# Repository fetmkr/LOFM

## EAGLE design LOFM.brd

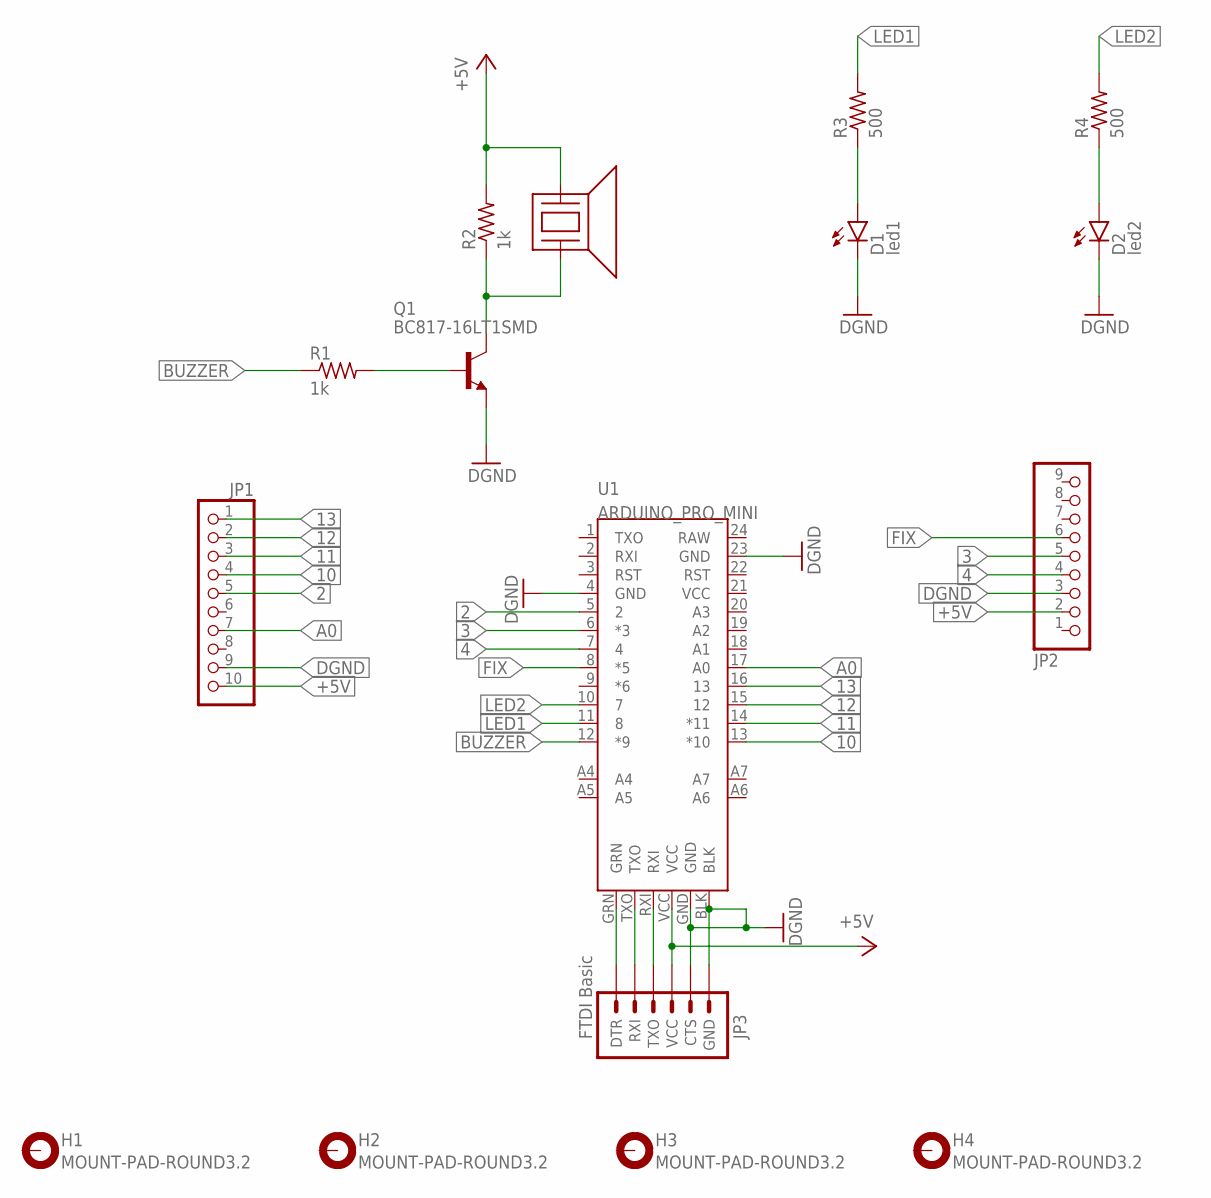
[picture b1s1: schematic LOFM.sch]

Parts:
D1: led1; LED3MM
D2: led2; LED3MM
H1, H2, H3, H4: MOUNT-PAD-ROUND3.2; 3,2-PAD
JP1: HEADER-1X1070MIL; 1X10_ROUND70
JP2: HEADER-1X970MIL; 1X09_ROUND_70
JP3: FTDI Basic; 1X06
Q1: BC817-16LT1SMD; SOT23-BEC
R1, R2: 1k; R0603(1608)
R3, R4: 500; R0603(1608)
U1: ARDUINO_PRO_MINI
U7: BUZZER; PS1240

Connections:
2: JP1.5, U1.5 (2)
3: JP2.5, U1.6 (*3)
4: JP2.4, U1.7 (4)
10: JP1.4, U1.13 (*10)
11: JP1.3, U1.14 (*11)
12: JP1.2, U1.15 (12)
13: JP1.1, U1.16 (13)
+5V: JP1.10, JP2.2, JP3.4 (VCC), R2.2, U1.VCC, U7.1
A0: JP1.7, U1.17 (A0)
BUZZER: R1.1, U1.12 (*9)
DGND: D1.K (C), D2.K (C), JP1.9, JP2.3, JP3.5 (CTS), JP3.6 (GND), Q1.E, U1.4 (GND), U1.23 (GND), U1.BLK, U1.GND
FIX: JP2.6, U1.8 (*5)
LED1: R3.2, U1.11 (8)
LED2: R4.2, U1.10 (7)
unnamed: Q1.B, R1.2
unnamed: Q1.C, R2.1, U7.2
unnamed: D1.A, R3.1
unnamed: D2.A, R4.1
unnamed: JP3.3 (TXO), U1.RXI
unnamed: JP3.2 (RXI), U1.TXO
unnamed: JP3.1 (DTR), U1.GRN

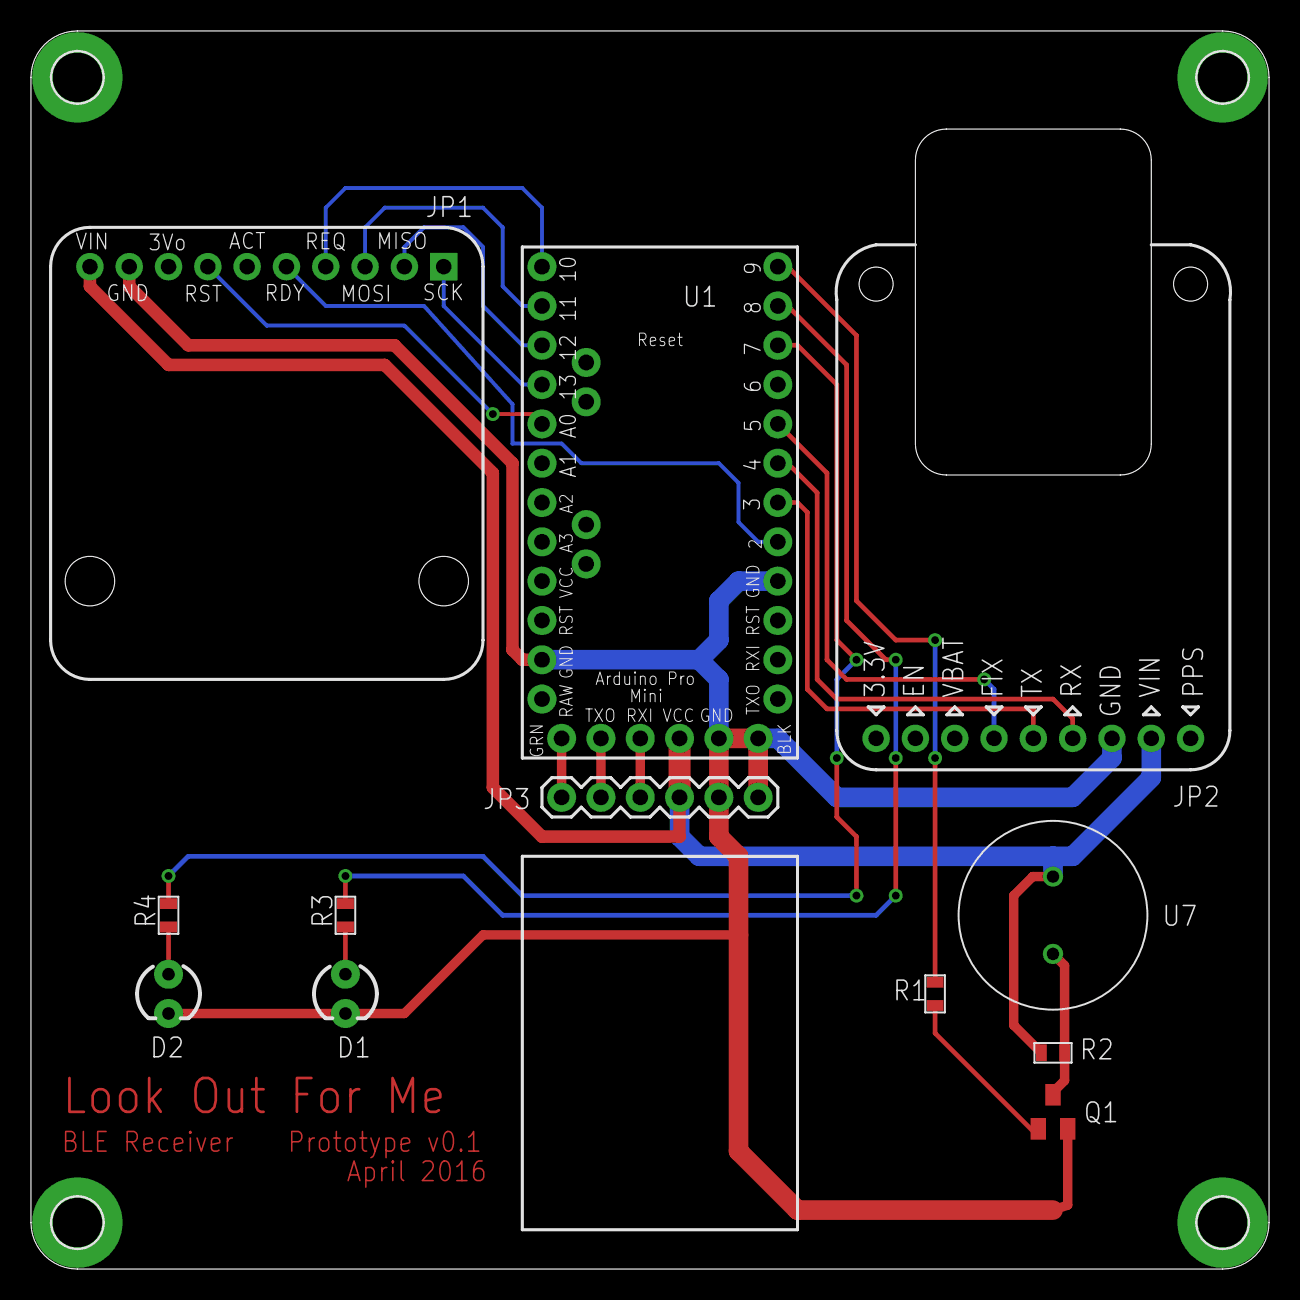
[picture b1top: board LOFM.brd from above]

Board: 2 copper layers, 80.0 x 80.0 mm, 16 parts (0 on the bottom side), 21 nets.

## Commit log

2016-04-05 :space_invader: Added .gitattributes
2016-04-05 first

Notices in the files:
parts and their libraries:
microbuilder: This work is placed in the public domain, and may be freely used for commercial and non-commercial work with the following conditions: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
SparkFun-LED: Licensing: Creative Commons ShareAlike 4.0 International - https://creativecommons.org/licenses/by-sa/4.0
